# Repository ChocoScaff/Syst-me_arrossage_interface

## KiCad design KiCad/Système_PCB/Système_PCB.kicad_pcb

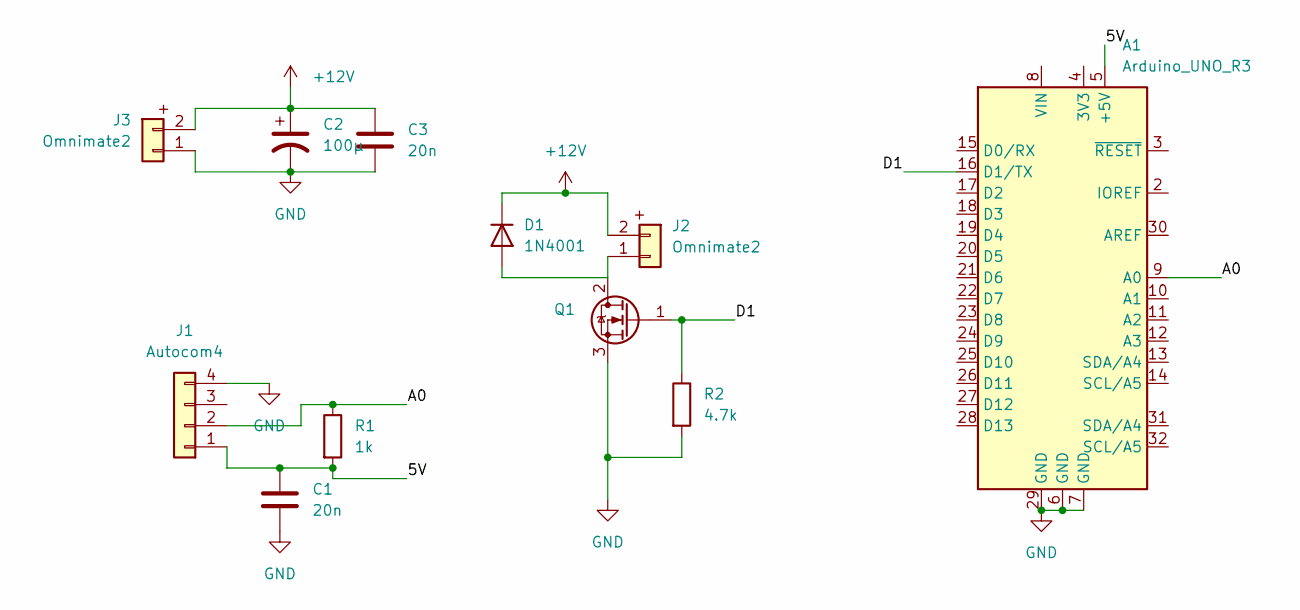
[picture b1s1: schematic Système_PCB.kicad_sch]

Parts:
A1: Arduino_UNO_R3
C1, C3: 20n; C_Rect_L7.0mm_W2.5mm_P5.00mm
C2: 100µ; CP_Radial_D5.0mm_P2.50mm
D1: 1N4001; D_DO-41_SOD81_P10.16mm_Horizontal
J1: Autocom4
J2, J3: Omnimate2; OmnimateSL-5,08_1x02_P5.08mm_Vertical
Q1: (no value)
R1: 1k; R_Axial_DIN0207_L6.3mm_D2.5mm_P10.16mm_Horizontal
R2: 4.7k; R_Axial_DIN0207_L6.3mm_D2.5mm_P10.16mm_Horizontal

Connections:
+12V: C2.1, C3.1, D1.1 (K), J2.2, J3.2
/5V: A1.5 (+5V), C1.1, J1.1, R1.2
/A0: A1.9 (A0), J1.2, R1.1
/D1: A1.16 (D1/TX), Q1.1 (G), R2.1
GND: A1.6 (GND), A1.7 (GND), A1.29 (GND), C1.2, C2.2, C3.2, J1.4, J3.1, Q1.3 (S), R2.2
unnamed: D1.2 (A), J2.1, Q1.2 (D)

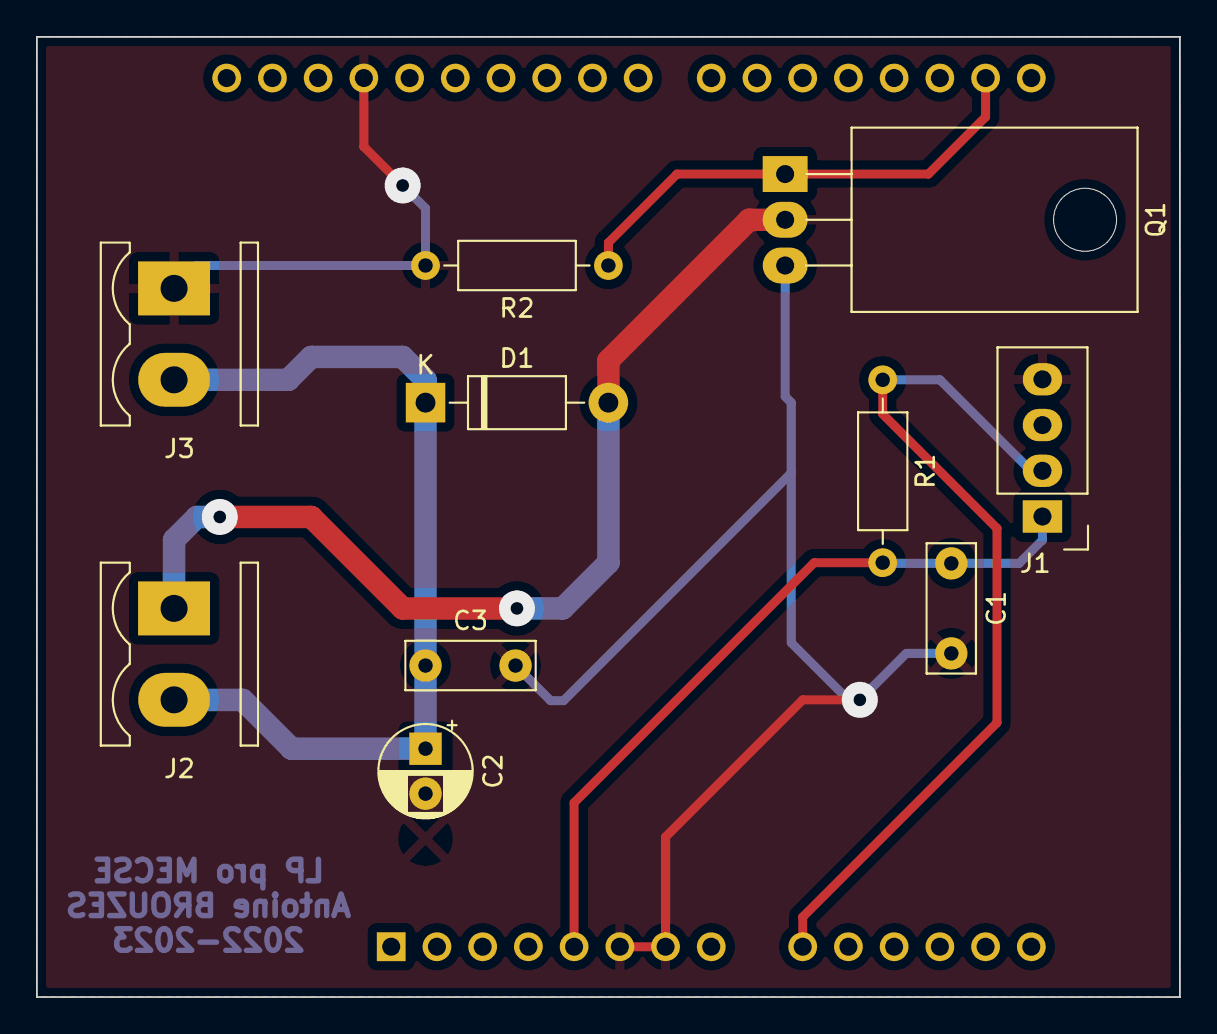
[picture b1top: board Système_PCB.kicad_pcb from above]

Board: 2 copper layers, 63.5 x 53.3 mm, 11 parts (1 on the bottom side), 6 nets.

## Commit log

2023-05-23 --Add Doc
2023-05-23 --Add Kicad Porject for PCB
2023-05-23 --Update Sheet PCB
2023-05-23 --Update PCB
2023-05-26 Change PCB
2023-05-26 Add VS code project
2023-05-26 -Add gerber files
2023-05-26 minor change
2023-05-31 -add PWM
2023-06-06 --Add DHT library
2023-06-07 Add read humidity on Terminal
2023-06-07 -Add humidity on screen
2023-06-13 Add tab and chart temp and humidity
2023-06-14 Add GUI
2023-06-20 Add comment
2023-06-20 Add doc
